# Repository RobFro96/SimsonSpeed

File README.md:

# SimsonSpeed
__Digitaler Tachometer, Drehzahlmesser und Ganganzeige für Simson-Mopeds__

Beschreibung des Grundprinzips: siehe <http://robert-fromm.info/?post=elec_simsonspeed>
Weitere Artikel auf meiner Homepage werden folgen.

# Inhalt des Repositories
## ccs-project/
Programmierung des MSP430. Code Composer Studio Projekt.

## eagle/
Schaltplan und Layout der Leiterplatte.

## gfx/
Bilddateien, Skripte zum Umwandeln der Bilddateien in Byte-Arrays zum Einfügen in C-Dateien.

## tester/
Platine mit Arduino Nano zum Simulieren der Lichtmaschine und Reed-Kontakt. Ermöglicht einfaches Testen der Anwendungen.

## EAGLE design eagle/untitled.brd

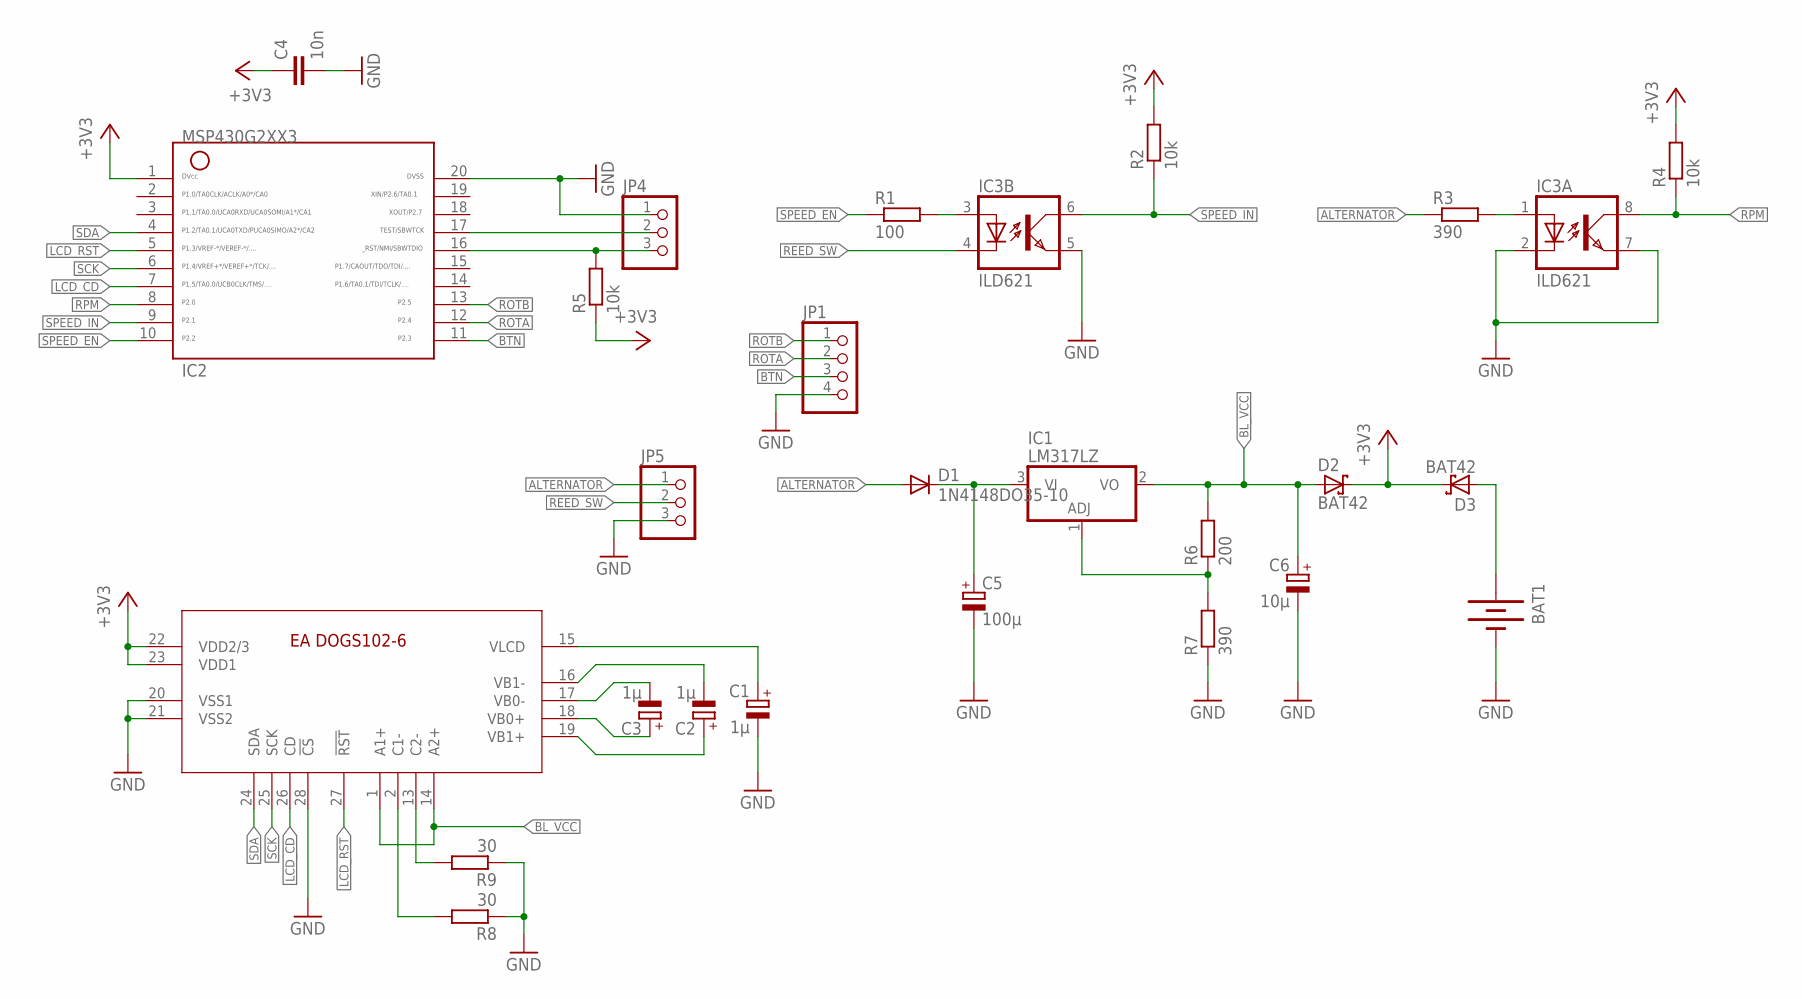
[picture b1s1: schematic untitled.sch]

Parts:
BAT1: BATTERY20PTH; BATTCOM_20MM_PTH
C1, C2, C3: 1µ; E2-4
C4: 10n; C050-024X044
C5: 100µ; E2,5-6E
C6: 10µ; E2-4
D1: 1N4148DO35-10; DO35-10
D2, D3: BAT42; DO35-10
IC1: LM317LZ; TO92
IC2: G2XX3---N20; N20
IC3: ILD621; DIL08
JP1: PINHD-1X4; 1X04
JP4, JP5: PINHD-1X3; 1X03
R1: 100; 0204/7
R2, R4, R5: 10k; 0204/7
R3, R7: 390; 0204/7
R6: 200; 0204/7
R8, R9: 30; 0204/7
U$1: EA-DOG102-6; EA_DOGS102-6

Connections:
+3V3: C4.1, D2.C, D3.C, IC2.1, R2.2, R4.2, R5.1, U$1.22 (VDD2/3), U$1.23 (VDD1)
ALTERNATOR: D1.A, JP5.1, R3.1
BL_VCC: C6.+, D2.A, IC1.2 (VO), R6.2, U$1.1 (A1+), U$1.14 (A2+)
BTN: IC2.11, JP1.3
GND: BAT1.2 (-), C1.-, C4.2, C5.-, C6.-, IC2.20, IC3.2 (C), IC3.5 (EMIT), IC3.7 (EMIT), JP1.4, JP4.1, JP5.3, R7.1, R8.1, R9.1, U$1.20 (VSS1), U$1.21 (VSS2), U$1.28 (!CS!)
LCD_CD: IC2.7, U$1.26 (CD)
LCD_RST: IC2.5, U$1.27 (!RST!)
unnamed: IC2.16, JP4.3, R5.2
unnamed: IC2.17, JP4.2
unnamed: C1.+, U$1.15 (VLCD)
unnamed: IC3.3 (A), R1.2
unnamed: C3.-, U$1.17 (VB0-)
unnamed: C3.+, U$1.18 (VB0+)
unnamed: C2.-, U$1.16 (VB1-)
unnamed: IC1.1 (ADJ), R6.1, R7.2
unnamed: C5.+, D1.C, IC1.3 (VI)
unnamed: BAT1.1 (+), D3.A
unnamed: IC3.1 (A), R3.2
unnamed: C2.+, U$1.19 (VB1+)
unnamed: R8.2, U$1.2 (C1-)
unnamed: R9.2, U$1.13 (C2-)
REED_SW: IC3.4 (C), JP5.2
ROTA: IC2.12, JP1.2
ROTB: IC2.13, JP1.1
RPM: IC2.8, IC3.8 (COL), R4.1
SCK: IC2.6, U$1.25 (SCK)
SDA: IC2.4, U$1.24 (SDA)
SPEED_EN: IC2.10, R1.1
SPEED_IN: IC2.9, IC3.6 (COL), R2.1

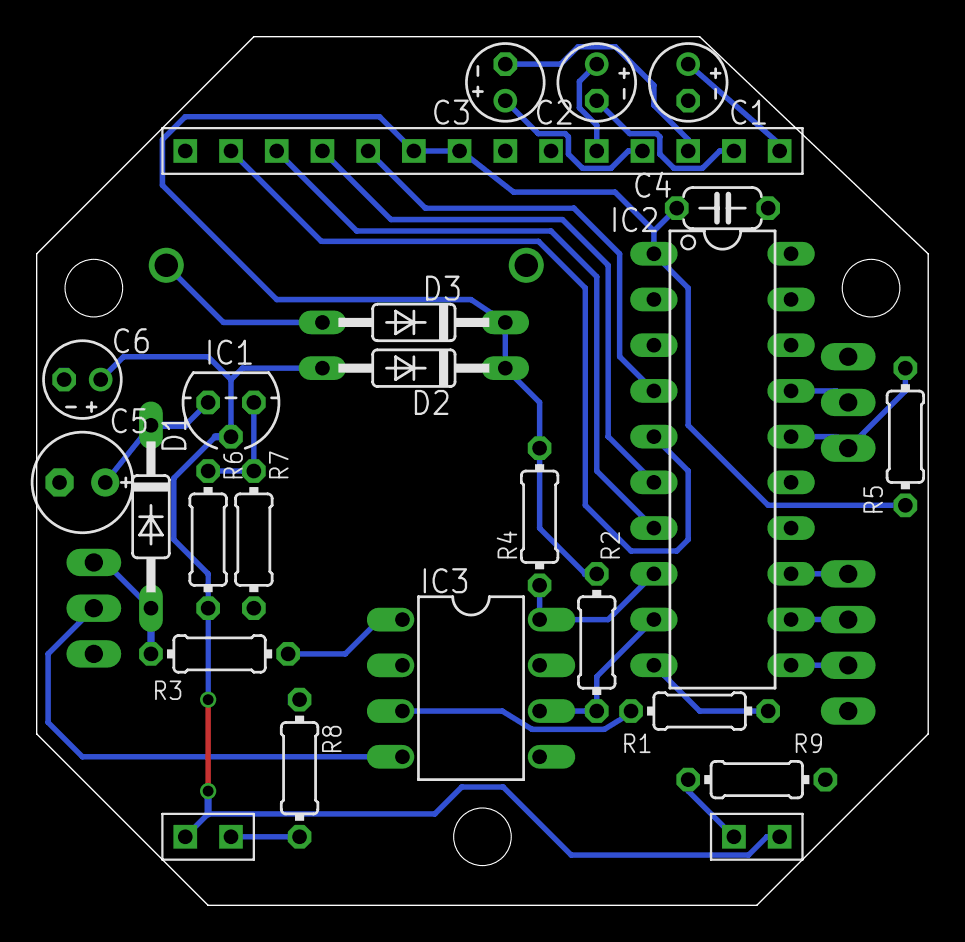
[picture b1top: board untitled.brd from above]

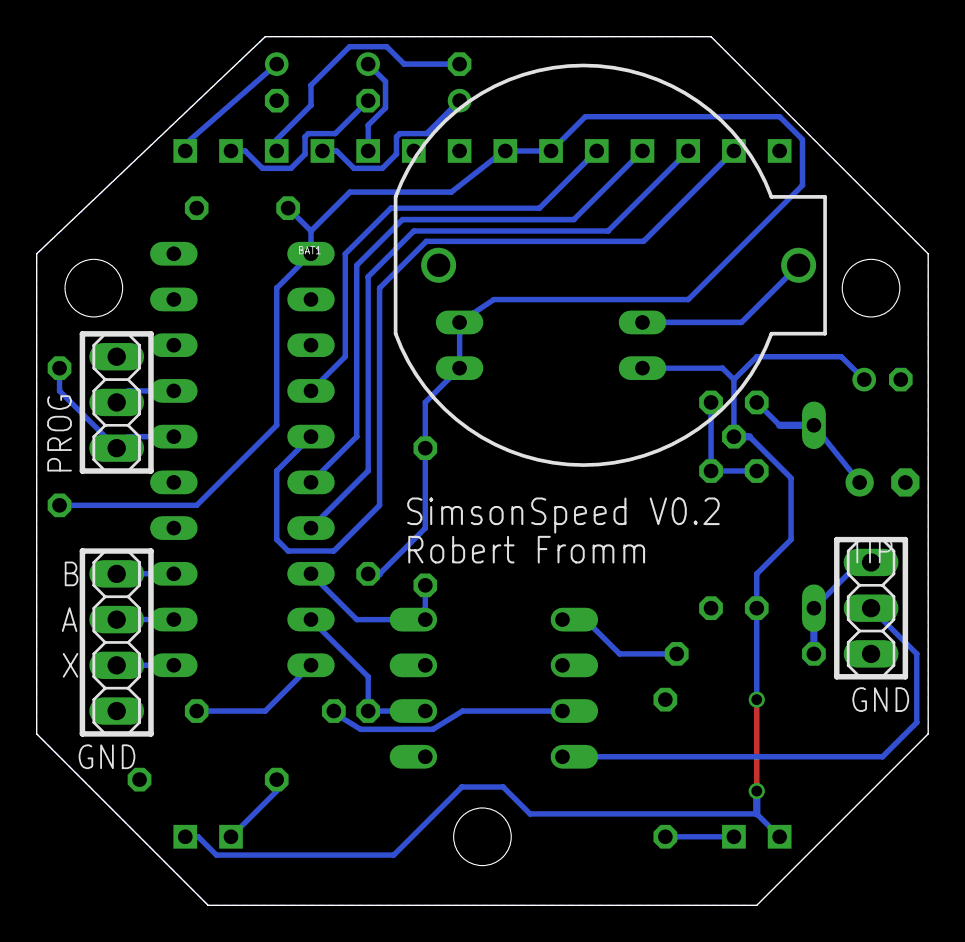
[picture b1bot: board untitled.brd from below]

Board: 2 copper layers, 49.5 x 48.3 mm, 26 parts (4 on the bottom side), 29 nets.

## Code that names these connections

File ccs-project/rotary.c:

#include <msp430.h>
#include <stdint.h>
#include "power.h"
#include "timer.h"

#include "rotary.h"


volatile uint8_t rotary_pressed = 0; //!< Gibt, an ob der Rotary gedrückt wurde. Muss manuell resettet werden.
volatile int16_t rotary_counter = 0; //!< Gibt die aktuelle Position des Drehgebers an. Kann manipuliert werden.

/**
 * Initialisierung der Rotary-Ansteuerung
 * Initialisierung der drei Pins, des Timers A0
 */
void rotary_init() {
	P2DIR &= ~(BIT3 + BIT4 + BIT5);
	P2REN |= (BIT3 + BIT4 + BIT5);
	P2OUT |= (BIT3 + BIT4 + BIT5);

	P2IE |= BIT3 + BIT4;
	P2IES &= ~(BIT3 + BIT4 + BIT5);
	P2IFG &= ~(BIT3 + BIT4 + BIT5);

	TA0CCTL0 = CCIE;
	TA0CCR0 = 100;
}

/**
 * Ausschalten der Pullups zum Stromsparen,
 * Ausschalten des Timer A0
 */
void rotary_disable() {
	P2IE &= ~(BIT4 + BIT5);
	P2OUT &= ~(BIT4 + BIT5);

	TA0CTL = 0;
}

/**
 * ISR für Port 2
 *
 * Pin 2.0 (RPM): Aufwachen im StandBy
 * Pin 2.3 (BTN): Aufwachen im StandBy, rotary_pressed setzen (Normalbetrieb)
 * Pin 2.4 (ROTA): Starten des Timers A0
 */
#pragma vector=PORT2_VECTOR
interrupt void PORT2_ISR() {
	// RPM-Pin
	if (P2IFG & BIT0) {
		P2IFG &= ~BIT0;
		if (power_sleeping) {
			__low_power_mode_off_on_exit();
		}
	}

	// Button
	if (P2IFG & BIT3) {
		P2IFG &= ~BIT3;
		if (power_sleeping) {
			__low_power_mode_off_on_exit();
		} else if (rpm_periodes[0] == 0xffff) {
			rotary_pressed = 1;
		}
	}

	// Rotary
	if (P2IFG & BIT4) {
		P2IFG &= ~BIT4;

		if (!(TA0CTL & MC_1)) {
			TA0CTL = TASSEL_2 + ID_3 + TACLR + MC_1;
		}
	}
}

/**
 * Timer A0 CCR0-Interrupt
 * Wird ausgelöst 800 µsec nach fallender Flanke an ROTA
 */
#pragma vector=TIMER0_A0_VECTOR
interrupt void TIMER0_A0_ISR() {
	TA0CTL = 0;

	if (rpm_periodes[0] != 0xffff)
		return;

	if (P2IN & BIT4) {
		if (P2IN & BIT5) {
			rotary_counter++;
		} else {
			rotary_counter--;
		}
	}

	P2IE |= BIT4;
}

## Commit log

2017-06-29 Initial Push
2017-06-29 Added Trip
2017-07-01 Started Gear Display
2017-07-02 Finished Gear Display
2017-07-05 Finished Power-Manager
2017-07-08 Added Touch
2017-07-09 Minor Fixes, Changed Capacitive Touch to one button
2017-07-16 Minor Fixes
2017-11-03 What changed?
2017-11-03 Release Version 1.1 Changed Touch to Button
2018-03-31 Explicit Pullup on Push-Button
2018-03-31 Added Tester
2018-03-31 Added EAGLE files
2018-04-04 Added 8x6 font and string output to LCD
2018-04-06 CHANGE: Ziffern auf Schriftart Roboto Black umgestellt. ADD: Neues Anzeige-Design erstellt
2018-04-06 ADD: Readme, License
2018-04-06 CHANGE: Readme
2018-04-07 ADD: Kommentare (auch Doxygen) des gesamten MSP430-Programms
2018-04-07 ADD: Neues Design, Neue Position Ganganzeige implementiert
2018-04-08 ADD: Nochmal neues Design, komplett implementiert
2018-04-12 ADD: Rotary Controller-Ansteuerung
2018-04-12 STARTED: Submenu (Kleines Menu im Hauptbildschirm)
2018-04-14 STARTED: Einstellungsmenü
2018-04-15 CHANGE: Unterordner lcd/ und mainscreen/ erstellt
2018-04-15 ADD: Dicke Schriftart
2018-04-16 CONTINUED: Zeichen des Einstellungsmenu
2018-04-24 [FINISH] Einstellungsmenü
2018-04-25 Release 0.2

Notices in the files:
parts and their libraries:
SparkFun-Electromechanical: Licensing: Creative Commons ShareAlike 4.0 International - https://creativecommons.org/licenses/by-sa/4.0
